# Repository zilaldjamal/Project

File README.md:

# Project
 My electronic project

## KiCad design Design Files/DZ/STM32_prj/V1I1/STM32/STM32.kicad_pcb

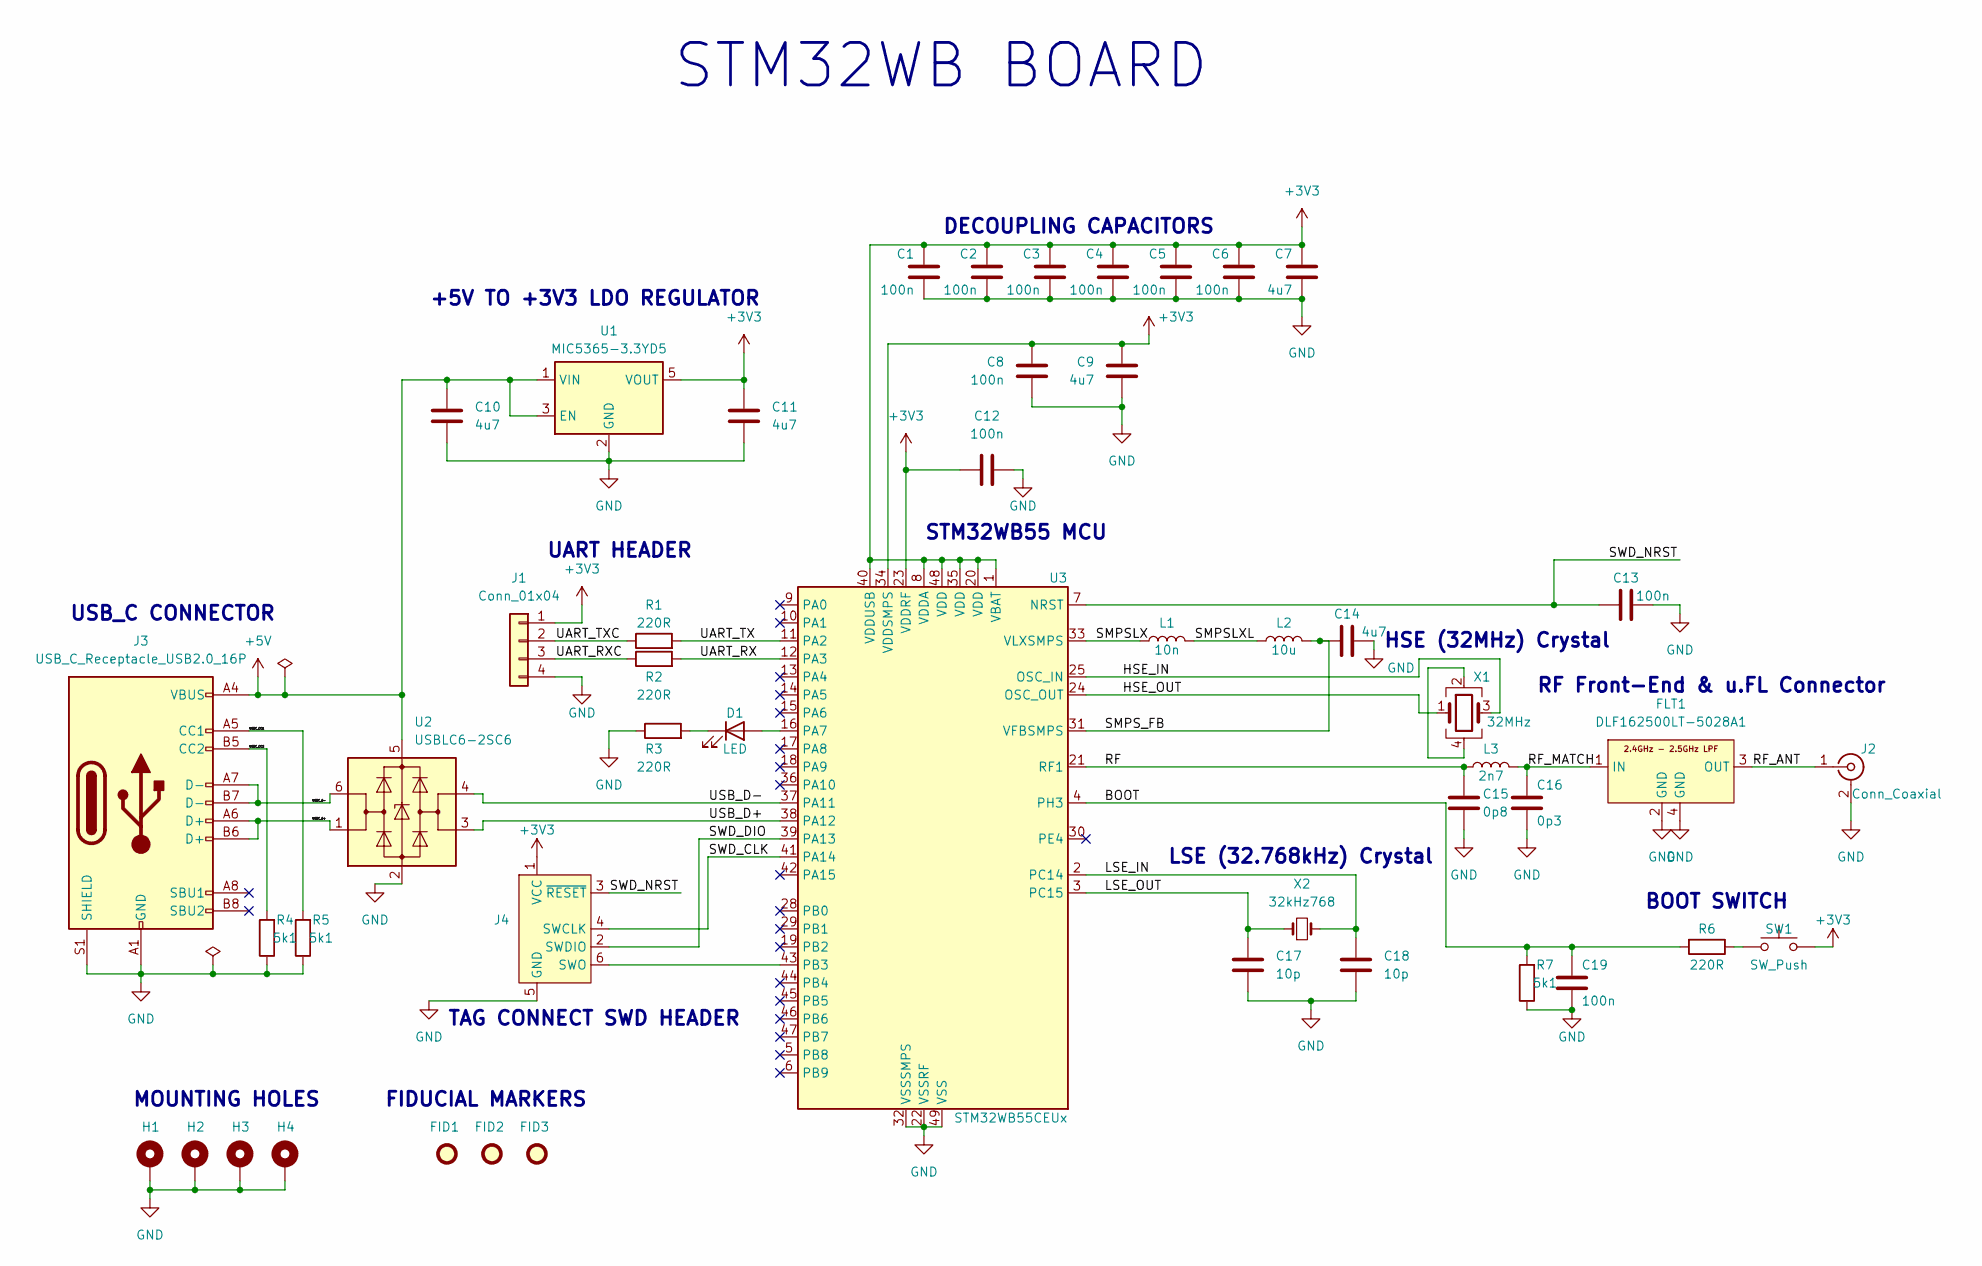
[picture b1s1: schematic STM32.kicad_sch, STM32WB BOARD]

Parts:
C1, C2, C3, C4, C5, C6, C8, C12, C13, C19: 100n; C_0402_1005Metric
C7, C9, C10, C11, C14: 4u7; C_0603_1608Metric
C15: 0p8; C_0402_1005Metric
C16: 0p3; C_0402_1005Metric
C17, C18: 10p; C_0402_1005Metric
D1: LED; LED_0402_1005Metric
FID1, FID2, FID3: Fiducial; Fiducial_1mm_Mask2mm
FLT1: DLF162500LT-5028A1
H1, H2, H3, H4: MountingHole_Pad; MountingHole_2.2mm_M2_Pad
J1: Conn_01x04; Molex_PicoBlade_53048-0410_1x04_P1.25mm_Horizontal
J2: Conn_Coaxial; U.FL_Hirose_U.FL-R-SMT-1_Vertical
J3: USB_C_Receptacle_USB2.0_16P; USB_C_Receptacle_GCT_USB4105-xx-A_16P_TopMnt_Horizontal
J4: Conn_ARM_SWD_TagConnect_TC2030; Tag-Connect_TC2030-IDC-FP_2x03_P1.27mm_Vertical
L1: 10n; L_0402_1005Metric
L2: 10u; L_0805_2012Metric
L3: 2n7; L_0402_1005Metric
R1, R2, R3, R6: 220R; R_0402_1005Metric
R4, R5, R7: 5k1; R_0402_1005Metric
SW1: SW_Push; SW_SPST_CK_RS282G05A3
U1: MIC5365-3.3YD5; SOT-23-5
U2: USBLC6-2SC6; SOT-23-6
U3: STM32WB55CEUx; QFN-48-1EP_7x7mm_P0.5mm_EP5.6x5.6mm
X1: 32MHz; Crystal_SMD_2016-4Pin_2.0x1.6mm
X2: 32kHz768; Crystal_SMD_2012-2Pin_2.0x1.2mm

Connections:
+3V3: C1.1, C2.1, C3.1, C4.1, C5.1, C6.1, C7.1, C8.1, C9.1, C11.1, C12.1, J1.1, J4.1 (VCC), SW1.2, U1.5 (VOUT), U3.1 (VBAT), U3.8 (VDDA), U3.20 (VDD), U3.23 (VDDRF), U3.34 (VDDSMPS), U3.35 (VDD), U3.40 (VDDUSB), U3.48 (VDD)
+5V: C10.1, J3.A4 (VBUS), J3.A9 (VBUS), J3.B4 (VBUS), J3.B9 (VBUS), U1.1 (VIN), U1.3 (EN), U2.5 (VBUS)
/BOOT: C19.1, R6.2, R7.2, U3.4 (PH3)
/HSE_IN: U3.25 (OSC_IN), X1.3
/HSE_OUT: U3.24 (OSC_OUT), X1.1
/LSE_IN: C18.1, U3.2 (PC14), X2.2
/LSE_OUT: C17.1, U3.3 (PC15), X2.1
/RF: C15.1, L3.1, U3.21 (RF1)
/RF_ANT: FLT1.3 (OUT), J2.1 (In)
/RF_MATCH: C16.1, FLT1.1 (IN), L3.2
/SMPSLX: L1.1, U3.33 (VLXSMPS)
/SMPSLXL: L1.2, L2.1
/SMPS_FB: C14.1, L2.2, U3.31 (VFBSMPS)
/SWD_CLK: J4.4 (SWCLK), U3.41 (PA14)
/SWD_DIO: J4.2 (SWDIO), U3.39 (PA13)
/SWD_NRST: C13.1, J4.3 (~RESET), U3.7 (NRST)
/UART_RX: R2.2, U3.12 (PA3)
/UART_RXC: J1.3, R2.1
/UART_TX: R1.2, U3.11 (PA2)
/UART_TXC: J1.2, R1.1
/USBC_CC1: J3.A5 (CC1), R5.2
/USBC_CC2: J3.B5 (CC2), R4.2
/USBC_D+: J3.A6 (D+), J3.B6 (D+), U2.1 (I/O1)
/USBC_D-: J3.A7 (D-), J3.B7 (D-), U2.6 (I/O1)
/USB_D+: U2.3 (I/O2), U3.38 (PA12)
/USB_D-: U2.4 (I/O2), U3.37 (PA11)
GND: C1.2, C2.2, C3.2, C4.2, C5.2, C6.2, C7.2, C8.2, C9.2, C10.2, C11.2, C12.2, C13.2, C14.2, C15.2, C16.2, C17.2, C18.2, C19.2, FLT1.2 (GND), FLT1.4 (GND), H1.1, H2.1, H3.1, H4.1, J1.4, J2.2 (Ext), J3.A1 (GND), J3.A12 (GND), J3.B1 (GND), J3.B12 (GND), J3.S1 (SHIELD), J4.5 (GND), R3.1, R4.1, R5.1, R7.1, U1.2 (GND), U2.2 (GND), U3.22 (VSSRF), U3.32 (VSSSMPS), U3.49 (VSS)
unnamed: D1.2 (A), U3.16 (PA7)
unnamed: D1.1 (K), R3.2
unnamed: J4.6 (SWO), U3.43 (PB3)
unnamed: R6.1, SW1.1
unnamed: X1.2, X1.4

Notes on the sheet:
HSE (32MHz) Crystal
+5V TO +3V3 LDO REGULATOR
FIDUCIAL MARKERS
UART HEADER
${TITLE}
LSE (32.768kHz) Crystal
RF Front-End & u.FL Connector
TAG CONNECT SWD HEADER
MOUNTING HOLES
DECOUPLING CAPACITORS
STM32WB55 MCU
USB_C CONNECTOR
BOOT SWITCH

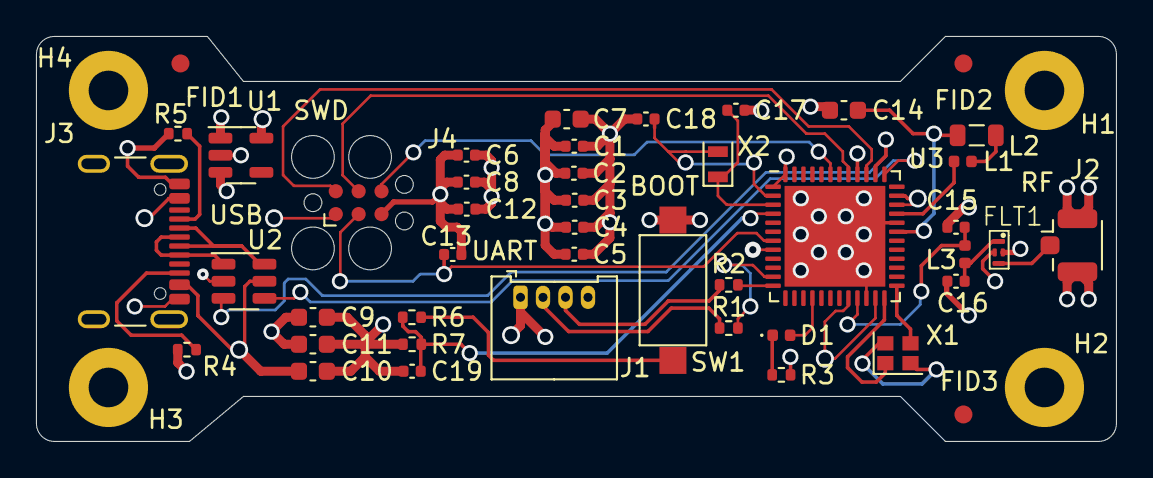
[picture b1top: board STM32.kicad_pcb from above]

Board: 4 copper layers, 60.0 x 22.5 mm, 48 parts (0 on the bottom side), 32 nets.

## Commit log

2024-02-21 Update 1
    - Created templates for Schematic and PCB Layout
2024-02-21 Update 2
    Set the files up
2024-02-23 Update 02
    SCH and PCB Design
2024-02-24 Update 03
    Project accomplished
2024-02-24 Update 4
    Errors fixed
